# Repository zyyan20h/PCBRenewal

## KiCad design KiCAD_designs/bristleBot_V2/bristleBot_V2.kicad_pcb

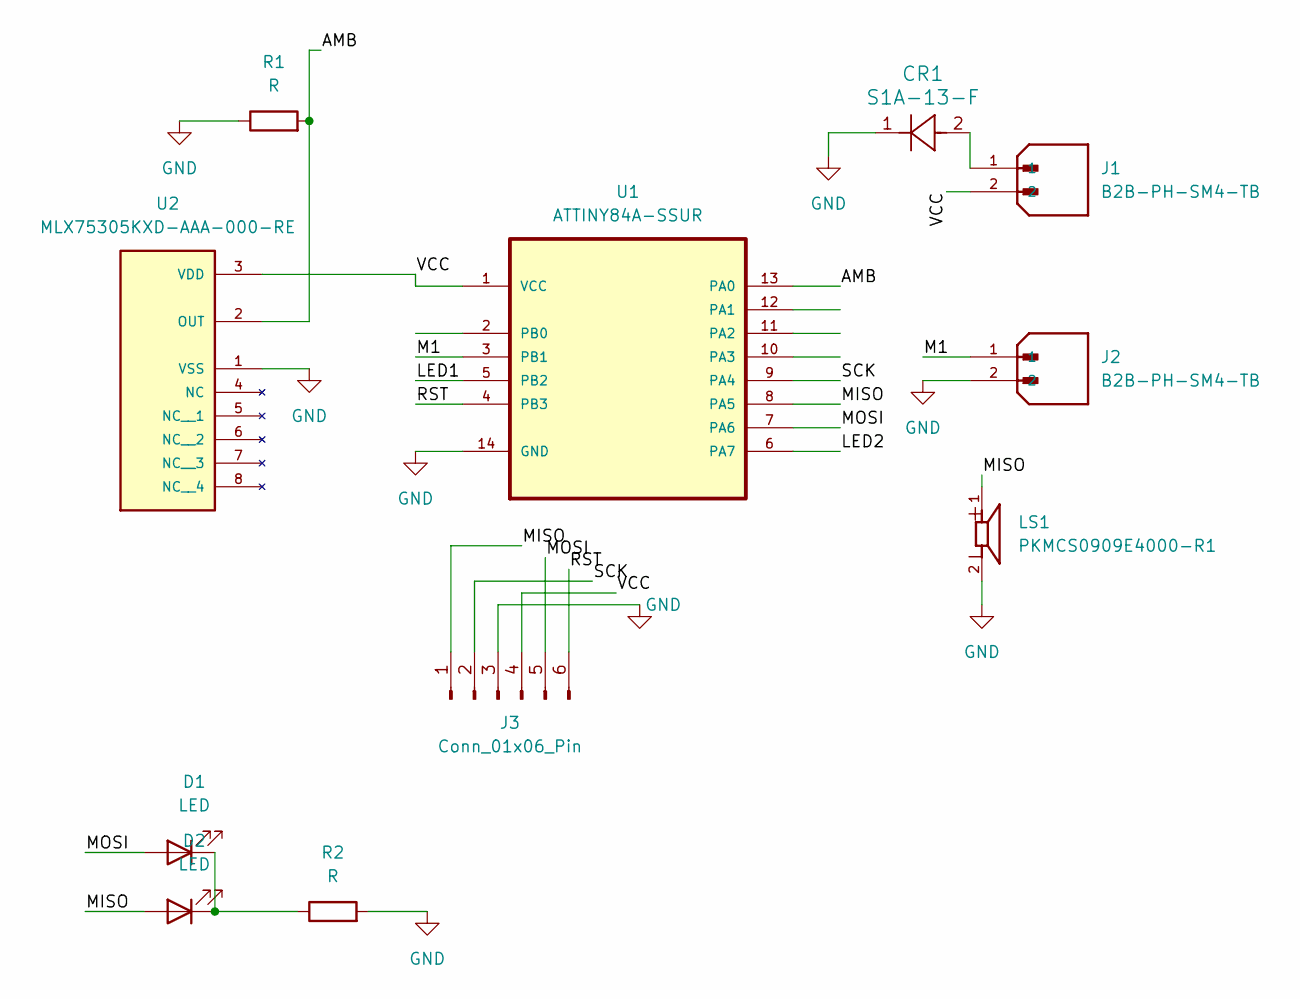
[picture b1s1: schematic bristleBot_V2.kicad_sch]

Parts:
CR1: S1A-13-F; SMA_DIO
D1, D2: LED; LED_1206_3216Metric
J1, J2: B2B-PH-SM4-TB; JST_B2B-PH-SM4-TB; PARTREV N/A
J3: Conn_01x06_Pin; PinHeader_1x06_P2.54mm_Horizontal
LS1: PKMCS0909E4000-R1; SPKR_PKMCS0909E4000-R1; PARTREV May 22, 2020
R1, R2: R; R_0805_2012Metric
U1: ATTINY84A-SSUR; SOIC127P600X175-14N; MPN ATTINY84A-SSUR
U2: MLX75305KXD-AAA-000-RE; SOIC127P599X175-8N; PARTREV REVISION 9 - OCTOBER 17, 2016

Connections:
/AMB: R1.2, U1.13 (PA0), U2.2 (OUT)
/LED1: U1.5 (PB2)
/LED2: U1.6 (PA7)
/M1: J2.1, U1.3 (PB1)
/MISO: D2.2 (A), J3.1, LS1.1, U1.8 (PA5)
/MOSI: D1.2 (A), J3.5, U1.7 (PA6)
/RST: J3.6, U1.4 (PB3)
/SCK: J3.2, U1.9 (PA4)
/VCC: J1.2, J3.4, U1.1 (VCC), U2.3 (VDD)
GND: CR1.1, J2.2, J3.3, LS1.2, R1.1, R2.2, U1.14 (GND), U2.1 (VSS)
unnamed: CR1.2, J1.1
unnamed: D1.1 (K), D2.1 (K), R2.1

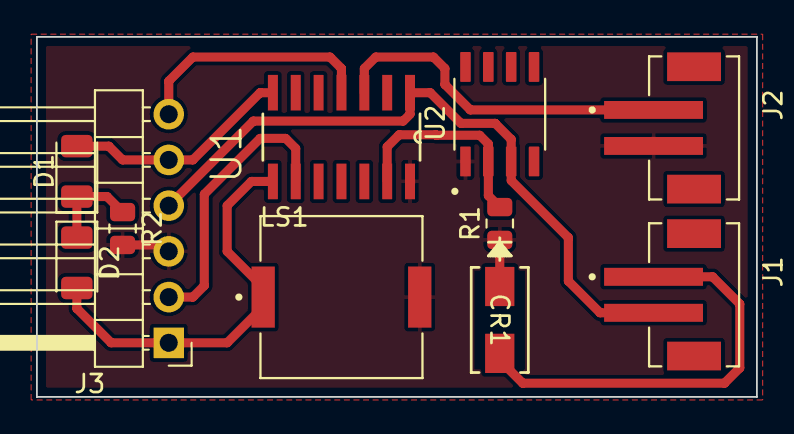
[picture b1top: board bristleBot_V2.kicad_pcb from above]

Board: 2 copper layers, 40.0 x 20.0 mm, 11 parts (0 on the bottom side), 10 nets.

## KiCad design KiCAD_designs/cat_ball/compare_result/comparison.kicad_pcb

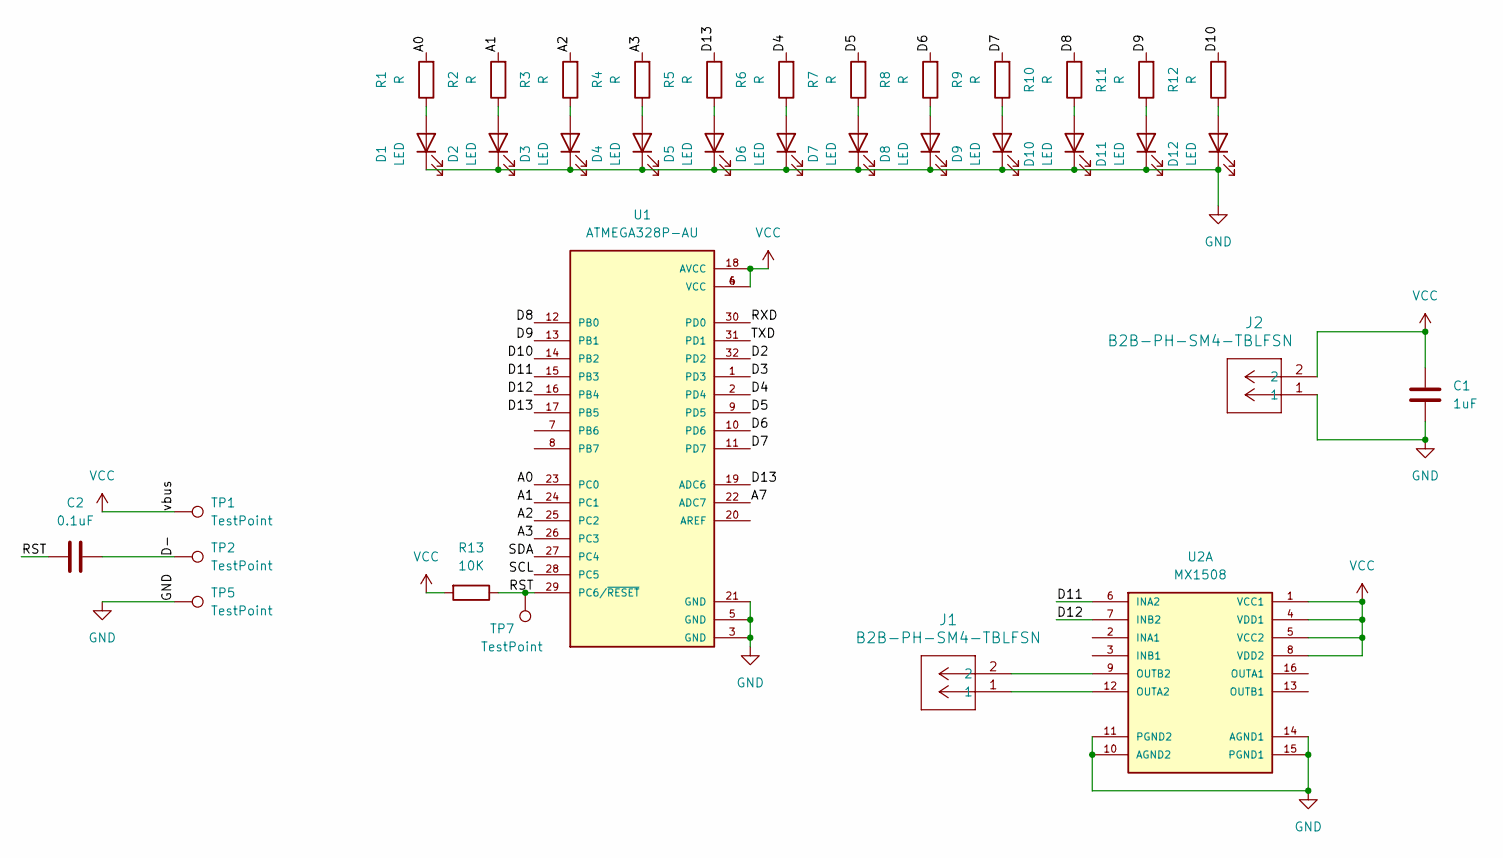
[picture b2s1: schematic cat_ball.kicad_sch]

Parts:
C1: 1uF; C_0805_2012Metric
C2: 0.1uF; C_0805_2012Metric
D1, D2, D3, D4, D5, D6, D7, D8, D9, D10, D11, D12: LED; LED_0603_1608Metric
J1, J2: B2B-PH-SM4-TBLFSN; B2B-PH-SM4-TBLFSN_JST
R1, R2, R3, R4, R5, R6, R7, R8, R9, R10, R11, R12: R; R_0603_1608Metric
R13: 10K; R_0603_1608Metric
TP1, TP2, TP5, TP7: TestPoint; TestPoint_Pad_D1.0mm
U1: ATMEGA328P-AU; atmega328P_shinked
U2: MX1508

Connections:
/A0: R1.2, U1.23 (PC0)
/A1: R2.2, U1.24 (PC1)
/A2: R3.2, U1.25 (PC2)
/A3: R4.2, U1.26 (PC3)
/A7: U1.22 (ADC7)
/D2: U1.32 (PD2)
/D3: U1.1 (PD3)
/D4: R6.2, U1.2 (PD4)
/D5: R7.2, U1.9 (PD5)
/D6: R8.2, U1.10 (PD6)
/D7: R9.2, U1.11 (PD7)
/D8: R10.2, U1.12 (PB0)
/D9: R11.2, U1.13 (PB1)
/D10: R12.2, U1.14 (PB2)
/D11: U1.15 (PB3), U2.6 (INA2)
/D12: U1.16 (PB4), U2.7 (INB2)
/D13: R5.2, U1.17 (PB5), U1.19 (ADC6)
/D-: C2.2, TP2.1
/RST: C2.1, R13.1, TP7.1, U1.29 (PC6/~RESET)
/RXD: U1.30 (PD0)
/SCL: U1.28 (PC5)
/SDA: U1.27 (PC4)
/TXD: U1.31 (PD1)
GND: C1.2, D1.1 (K), D2.1 (K), D3.1 (K), D4.1 (K), D5.1 (K), D6.1 (K), D7.1 (K), D8.1 (K), D9.1 (K), D10.1 (K), D11.1 (K), D12.1 (K), J2.1, TP5.1, U1.3 (GND), U1.5 (GND), U1.21 (GND), U2.10 (AGND2), U2.11 (PGND2), U2.14 (AGND1), U2.15 (PGND1)
unnamed: D1.2 (A), R1.1
unnamed: D2.2 (A), R2.1
unnamed: D3.2 (A), R3.1
unnamed: D4.2 (A), R4.1
unnamed: D5.2 (A), R5.1
unnamed: D6.2 (A), R6.1
unnamed: D7.2 (A), R7.1
unnamed: D8.2 (A), R8.1
unnamed: D9.2 (A), R9.1
unnamed: D10.2 (A), R10.1
unnamed: D11.2 (A), R11.1
unnamed: D12.2 (A), R12.1
unnamed: J1.1, U2.12 (OUTA2)
unnamed: J1.2, U2.9 (OUTB2)
VCC: C1.1, J2.2, R13.2, TP1.1, U1.4 (VCC), U1.6 (VCC), U1.18 (AVCC), U2.1 (VCC1), U2.4 (VDD1), U2.5 (VCC2), U2.8 (VDD2)

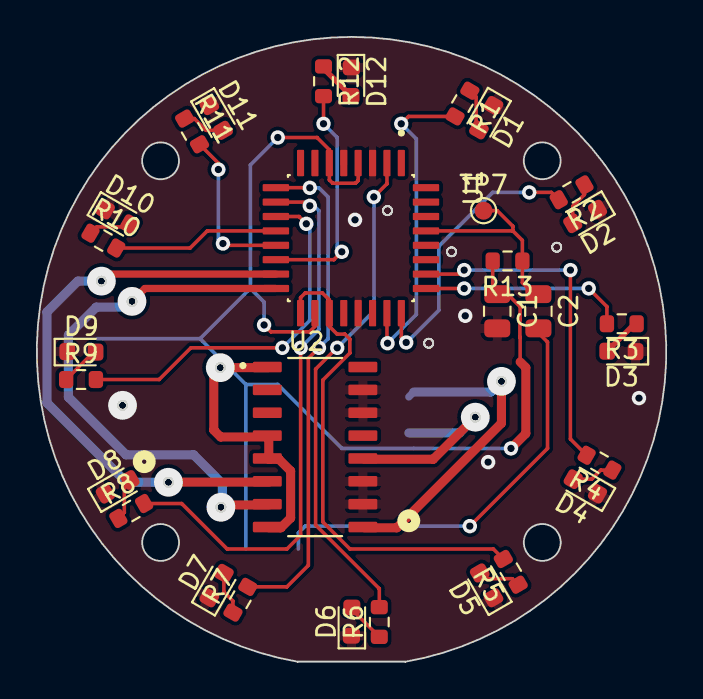
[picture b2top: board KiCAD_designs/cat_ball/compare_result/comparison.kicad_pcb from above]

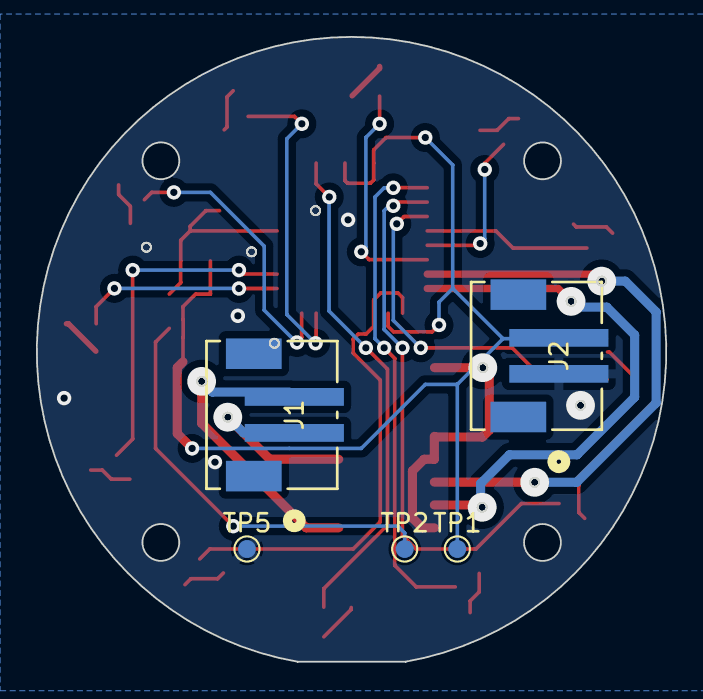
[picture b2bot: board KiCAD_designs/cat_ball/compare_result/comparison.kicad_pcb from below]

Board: 2 copper layers, 35.0 x 34.7 mm, 35 parts (5 on the bottom side), 32 nets.

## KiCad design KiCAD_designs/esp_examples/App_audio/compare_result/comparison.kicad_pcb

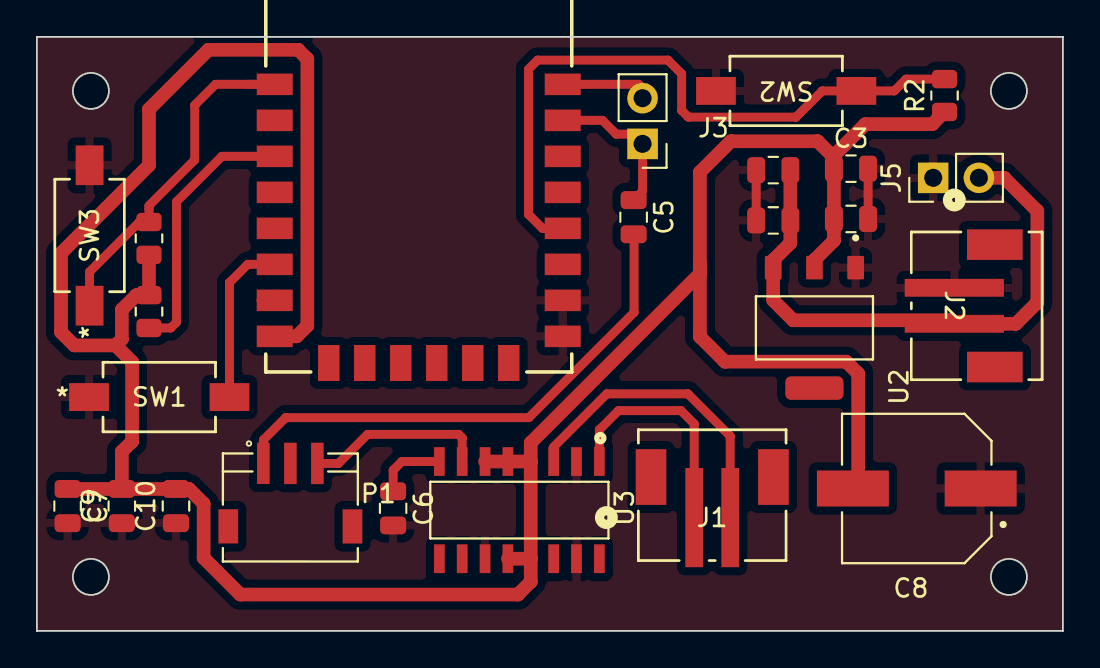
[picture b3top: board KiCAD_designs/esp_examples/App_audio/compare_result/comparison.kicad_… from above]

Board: 2 copper layers, 57.0 x 33.0 mm, 24 parts (0 on the bottom side), 14 nets.

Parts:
C1, C2, C3, C4: C; C_0805_2012Metric
C5: 0.47u; C_0805_2012Metric
C6: 0.1u; C_0805_2012Metric
C7, C9, C10: 1u; C_0805_2012Metric
C8: 470u; CAP_EEEFP1C471AL
J1, J2: B2B-PH-SM4-TBLFSN; B2B-PH-SM4-TBLFSN_JST
J3, J5: Conn_01x02_Pin; PinHeader_1x02_P2.54mm_Vertical
P1: S3B-ZR-SM4A-TF; JST_S3B-ZR-SM4A-TF
R1, R2, R4: R; R_0805_2012Metric
SW1, SW2, SW3: RS-282G05A3-SM RT; RS-282G05A3-SM RT_CNK
U1: ESP-12F
U2: AMS1117-3.3; SOT229P700X180-4N
U3: PAM8403DR; PAM8403

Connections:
/INL: C5.1, J3.1, U1.21 (RXD)
/RST: R1.1, SW3.1, U1.1 (RST)
/VIN: C1.2, C2.2, J2.2, J5.2, U2.3 (VIN)
/boot: R2.2, SW2.1, U1.18 (GPIO0)
GND: C1.1, C2.1, C3.2, C4.2, C6.2, C7.2, C8.1, C9.1, C10.1, J2.1, J5.1, SW1.1, SW2.2, SW3.2, U1.15 (GND), U1.16 (GPIO15), U2.1 (GND/ADJ), U3.2 (PGND@1), U3.11 (GND), U3.15 (PGND@2)
unnamed: C5.2, P1.1
unnamed: J3.2, U1.22 (TXD)
unnamed: R4.1, U1.3 (EN)
unnamed: SW1.2, U1.6 (GPIO12)
unnamed: J1.1, U3.1 (+OUT_L)
unnamed: J1.2, U3.3 (-OUT_L)
unnamed: P1.3, U3.7 (INL)
unnamed: C6.1, U3.8 (VREF)
VCC: C3.1, C4.1, C7.1, C8.2, C9.2, C10.2, R1.2, R2.1, R4.2, U1.8 (VCC), U2.2 (VOUT), U3.4 (PVDD@1), U3.5 (MUTE), U3.6 (VDD), U3.12 (SHND), U3.13 (PVDD@2)

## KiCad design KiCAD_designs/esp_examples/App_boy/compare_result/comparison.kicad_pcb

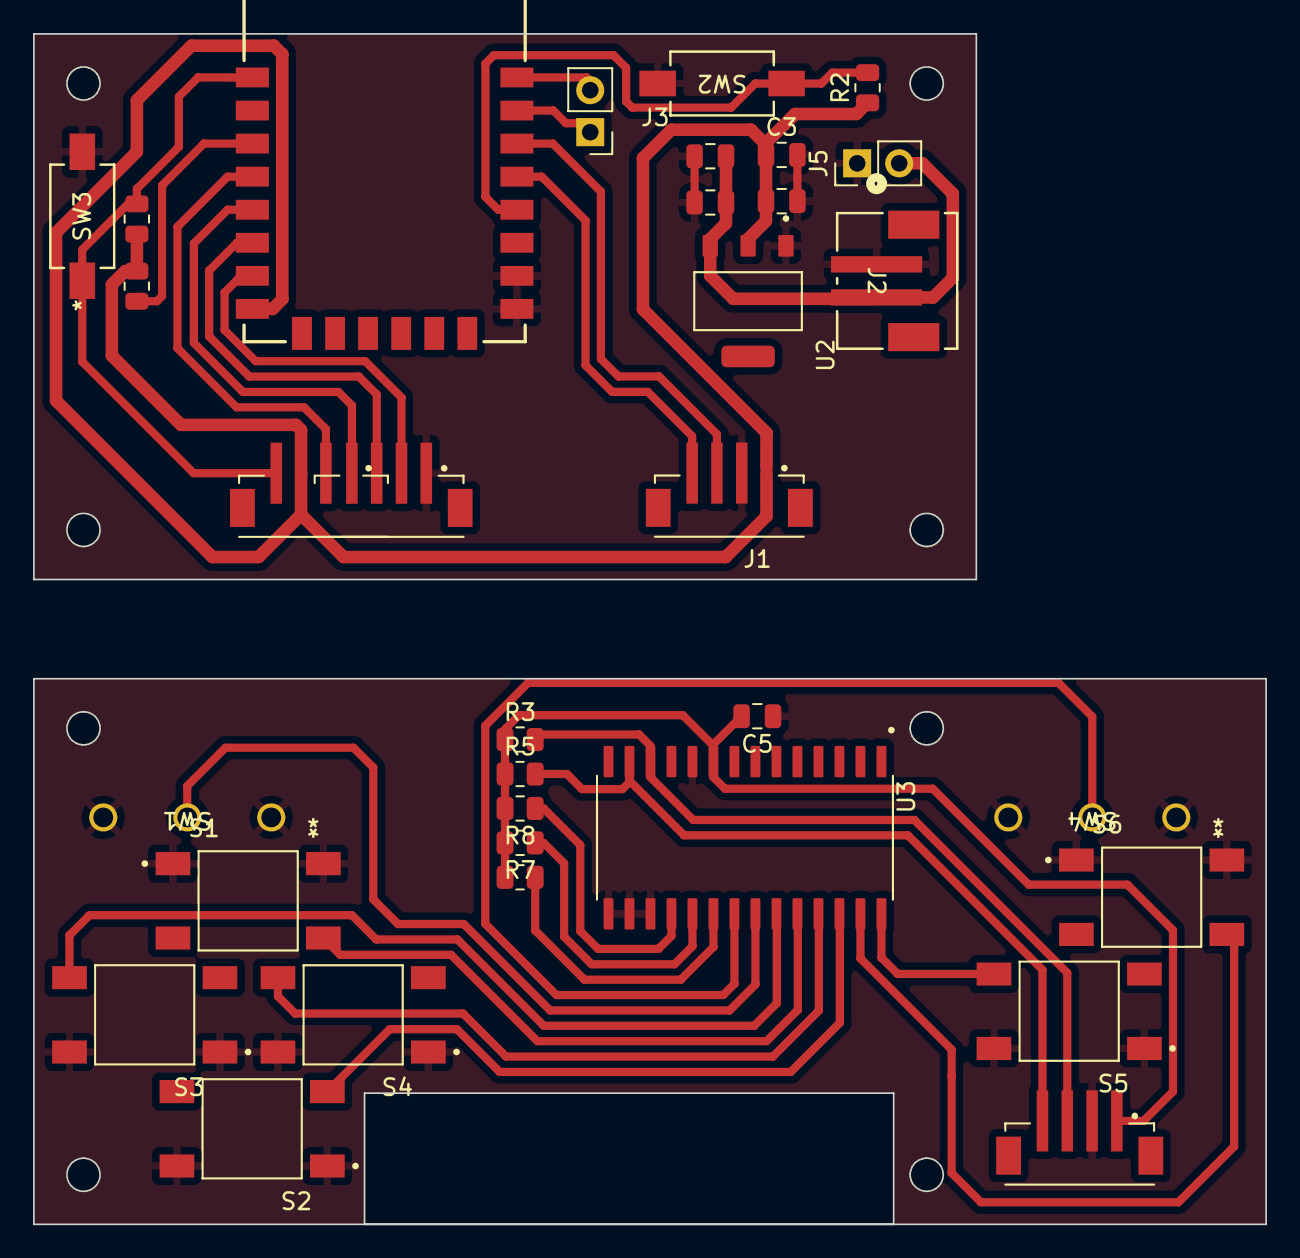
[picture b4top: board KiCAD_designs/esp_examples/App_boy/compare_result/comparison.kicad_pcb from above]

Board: 2 copper layers, 74.5 x 72.0 mm, 32 parts (0 on the bottom side), 27 nets.

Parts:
C1, C2, C3, C4, C5: C; C_0805_2012Metric
J1, J4: B4B-ZR-SM4-TFT_LF__SN_; JST_B4B-ZR-SM4-TFT_LF__SN_
J2: B2B-PH-SM4-TBLFSN; B2B-PH-SM4-TBLFSN_JST
J3, J5: Conn_01x02_Pin; PinHeader_1x02_P2.54mm_Vertical
J6: B7B-ZR-SM4-TFT_LF__SN_; B7B-ZR-SM4-TBLFSN_JST
R1, R2, R3, R4, R5, R6, R7, R8: R; R_0805_2012Metric
S1: up; switch_6
S2: down; switch_6
S3: left; switch_6
S4: right; switch_6
S5: A; switch_6
S6: B; switch_6
SW1, SW4: D2FS-FL-N-A; D2FS-FL-N-A_OMR
SW2, SW3: RS-282G05A3-SM RT; RS-282G05A3-SM RT_CNK
U1: ESP-12F
U2: AMS1117-3.3; SOT229P700X180-4N
U3: MCP23017-E_SO; MCP23017

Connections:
/A: S5.4, U3.28 (GPA7)
/AO: J6.5, U1.4 (GPIO16)
/B: S6.4, U3.27 (GPA6)
/CS: J6.3, U1.6 (GPIO12)
/RL: SW1.2, U3.22 (GPA1)
/RR: SW4.2, U3.21 (GPA0)
/RST: J6.7, R1.1, SW3.1, U1.1 (RST)
/SCK_mcp: J1.3, J4.3, R3.2, U1.20 (GPIO5), U3.12 (SCK)
/SCK_screen: J6.2, U1.7 (GPIO13)
/SDA_mcp: J1.4, J4.4, R5.2, U1.19 (GPIO4), U3.13 (SDA)
/SDA_screen: J6.4, U1.5 (GPIO14)
/VIN: C1.2, C2.2, J2.2, J5.2, U2.3 (VIN)
/boot: R2.2, SW2.1, U1.18 (GPIO0)
/down: S2.2, U3.26 (GPA5)
/left: S3.4, U3.23 (GPA2)
/right: S4.4, U3.25 (GPA4)
/up: S1.4, U3.24 (GPA3)
GND: C1.1, C2.1, C3.2, C4.2, C5.1, J1.2, J2.1, J4.2, J5.1, J6.1, S1.1, S1.3, S2.1, S2.3, S3.1, S3.3, S4.1, S4.3, S5.1, S5.3, S6.1, S6.3, SW1.1, SW1.3, SW2.2, SW3.2, SW4.1, SW4.3, U1.15 (GND), U1.16 (GPIO15), U2.1 (GND/ADJ), U3.10 (VSS), U3.15 (A0), U3.16 (A1), U3.17 (A2)
unnamed: J1.S1 (SHIELD), J1.S2 (SHIELD)
unnamed: J3.1, U1.21 (RXD)
unnamed: J3.2, U1.22 (TXD)
unnamed: J4.S1 (SHIELD), J4.S2 (SHIELD)
unnamed: R4.1, U1.3 (EN)
unnamed: R6.1, U3.20 (INTA)
unnamed: R7.1, U3.19 (INTB)
unnamed: R8.1, U3.18 (~RESET)
VCC: C3.1, C4.1, C5.2, J1.1, J4.1, J6.6, R1.2, R2.1, R3.1, R4.2, R5.1, R6.2, R7.2, R8.2, U1.8 (VCC), U2.2 (VOUT), U3.9 (VDD)
